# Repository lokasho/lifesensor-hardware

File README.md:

# lifesensor-hardware
Temporary repository for the next hardware generation of the CADUS Life Sensor.
Official repository at https://github.com/cadus/Life-Sensor.

## Similar projects and Resources:
- https://github.com/GliaX
- https://github.com/kitspace/awesome-electronics
- https://github.com/kitspace/kicad_footprints
- https://github.com/intajay/open-electronics

- ecg
    + https://github.com/xdever/MobilECG-II -> based on ADS1298
    + https://www.olimex.com/Products/Duino/Shields/SHIELD-EKG-EMG/open-source-hardware
    + https://www.electronicdesign.com/power-management/article/21798161/choose-the-right-resistors-for-medical-applications

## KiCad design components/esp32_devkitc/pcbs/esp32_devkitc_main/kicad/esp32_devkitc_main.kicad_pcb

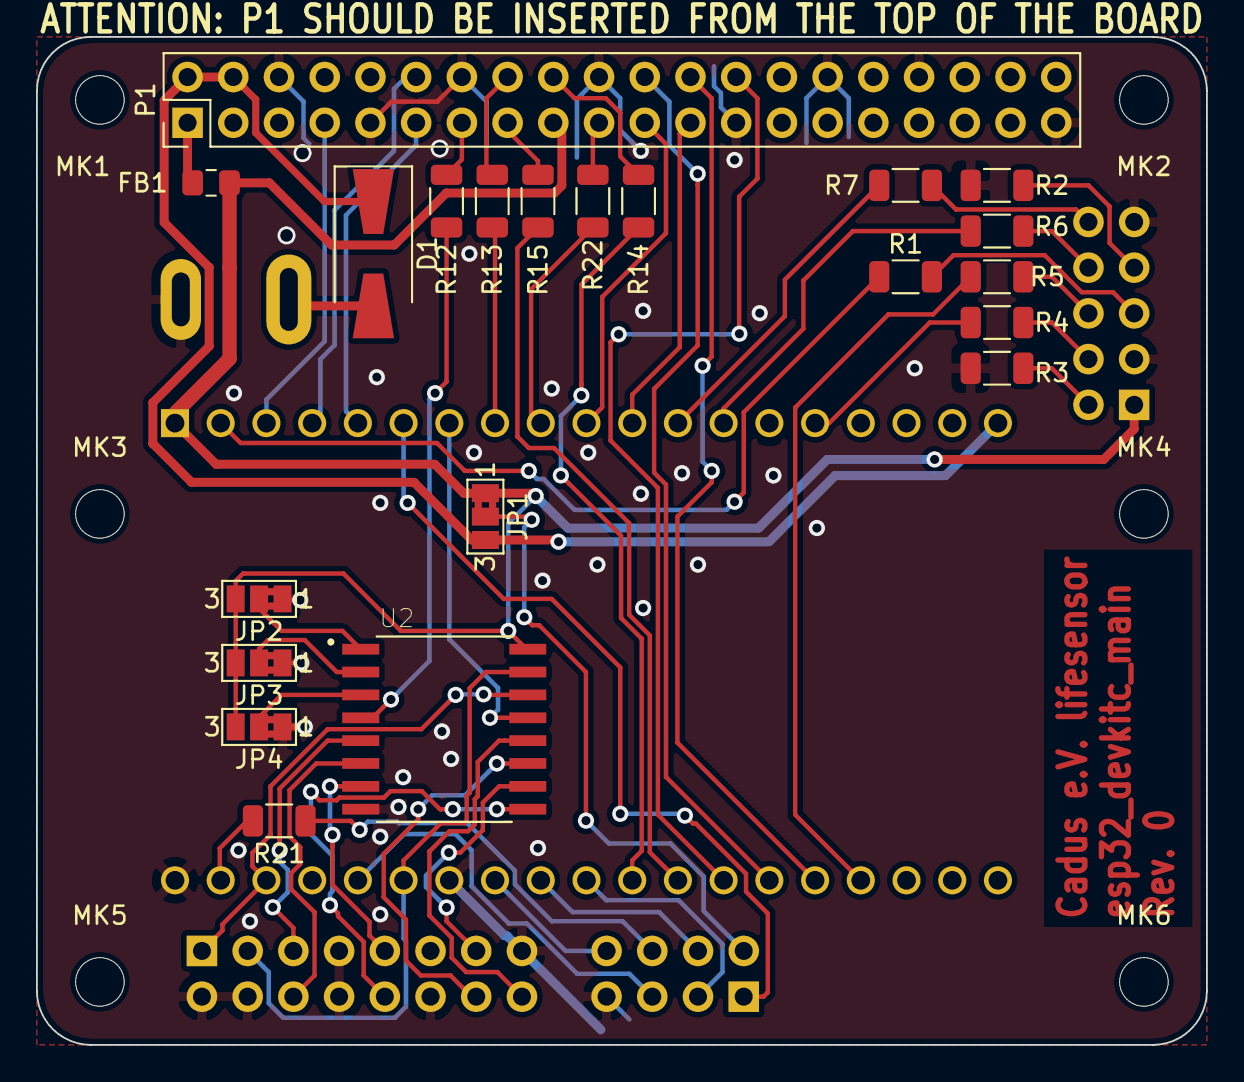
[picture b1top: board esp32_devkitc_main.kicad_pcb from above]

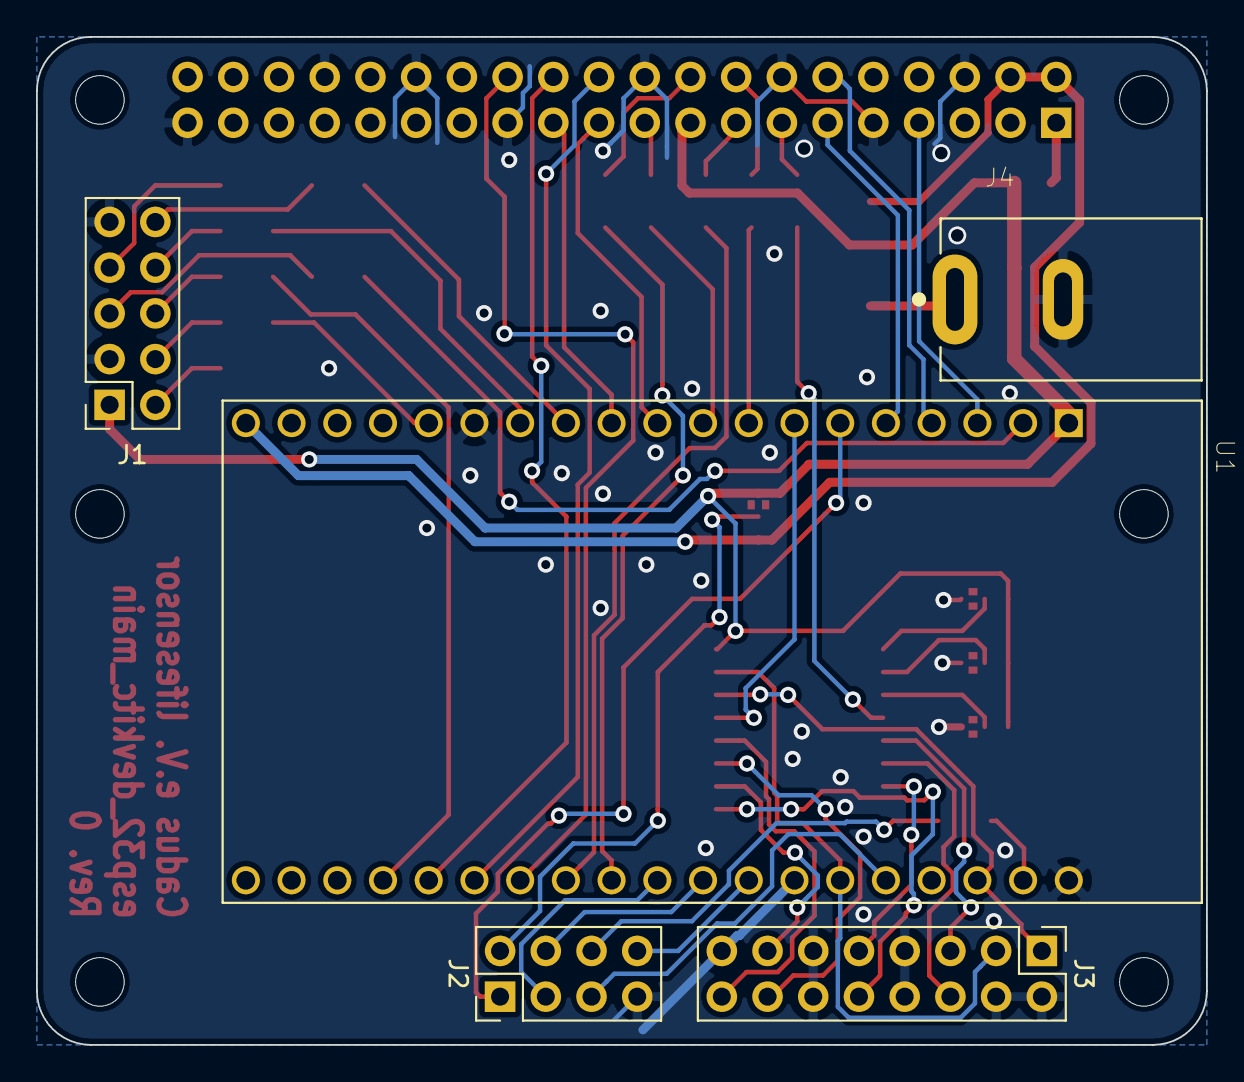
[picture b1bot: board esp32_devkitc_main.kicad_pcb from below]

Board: 2 copper layers, 65.0 x 56.0 mm, 32 parts (5 on the bottom side), 56 nets.

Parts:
D1: D; D_SMA-SMB_Universal_Handsoldering
FB1: Ferrite_Bead_Small; R_0805_2012Metric_Pad1.15x1.40mm_HandSolder
J1: Conn_02x05_Odd_Even; PinSocket_2x05_P2.54mm_Vertical
J2: Conn_02x04_Odd_Even; PinHeader_2x04_P2.54mm_Vertical
J3: Button/LED/I2C Connector; PinHeader_2x08_P2.54mm_Vertical
J4: CUI_PJ-102AH_Horizontal; CUI_PJ-037B
JP1, JP2, JP3, JP4: Jumper_NC_Dual; SolderJumper-3_P1.3mm_Bridged2Bar12_Pad1.0x1.5mm_NumberLabe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
MK1, MK2, MK3, MK4, MK5, MK6: M2.5; MountingHole_2.7mm_M2.5
P1: Conn_02x20_Odd_Even; PinHeader_2x20_P2.54mm_Vertical
R1, R3, R12, R13, R14, R15: 0; R_1206_3216Metric
R2: n.p.; R_1206_3216Metric
R4, R5, R6, R7, R21, R22: 100; R_1206_3216Metric
U1: ESP32-DEVKITC-32D; MODULE_ESP32-DEVKITC-32D
U2: PCF8574ADWR; SOIC127P1030X265-16N

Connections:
/5V_in: D1.2, J4.1
/DISP_CS_DISP: J2.3, U1.29
/DISP_CS_TOUCH: J2.5, U1.24
/DISP_INT_TOUCH: J2.1, U1.6
/DISP_MISO: J2.8, U1.27
/DISP_MOSI: J2.6, R21.1
/DISP_SCLK: J2.4, U1.28
/EXPGPIO1: J3.5, U2.5
/EXPGPIO2: J3.6, U2.6
/EXPGPIO3: J3.9, U2.7
/EXPGPIO4: J3.10, U2.9
/EXPGPIO5: J3.13, U2.10
/EXPGPIO6: J3.14, U2.11
/EXPGPIO7: J3.16, U2.12
/GPIOEXP_INT: U1.7, U2.13
/JTAG_RTCK: J1.2, R3.2
/JTAG_TCK: R4.1, U1.15
/JTAG_TDI: R6.1, U1.13
/JTAG_TDO: R5.1, U1.35
/JTAG_TMS: R7.1, U1.12
/JTAG_~SRST: J1.7, R2.1
/JTAG_~TRST: R1.1, U1.2
/PROC_SCL: J3.1, U1.22, U2.14
/PROC_SDA: J3.3, U1.25, U2.15
/SENS_3V3_ANA: FB1.2, P1.1
/SENS_3V3_DIG: FB1.1, J1.1, JP1.1, JP2.3, JP3.3, JP4.3, P1.17, U1.1, U2.16
/SENS_5V_ANA: D1.1, JP1.3, P1.2, P1.4, U1.19
/SENS_INT_BPM: P1.7, U1.3
/SENS_INT_ECG: P1.11, U1.5
/SENS_INT_SPO2: P1.12, U1.4
/SENS_MISO: P1.21, U1.10
/SENS_MOSI: P1.19, R22.1
/SENS_SCLK: P1.23, U1.11
/SENS_START: P1.13, R12.2
/~SENS_CS_BPM: P1.22, U1.33
/~SENS_CS_ECG: P1.24, U1.34
/~SENS_CS_SPO2: P1.26, U1.32
/~SENS_RST_BPM: P1.15, R15.2
/~SENS_RST_ECG: P1.16, R13.2
/~SENS_RST_SPO2: P1.18, R14.2
GND: J1.3, J1.9, J2.7, J3.2, J3.4, J3.7, J3.8, J3.11, J3.12, J3.15, J4.2, JP2.1, JP3.1, JP4.1, P1.6, P1.9, P1.14, P1.20, P1.25, P1.30, P1.34, P1.39, R2.2, R3.1, U1.14, U1.20, U1.26, U2.8
unnamed: J1.4, R4.2
unnamed: J1.5, R1.2
unnamed: J1.6, R5.2
unnamed: J1.8, R6.2
unnamed: J1.10, R7.2
unnamed: J2.2, JP1.2
unnamed: JP2.2, U2.1
unnamed: JP3.2, U2.2
unnamed: JP4.2, U2.3
unnamed: R12.1, U2.4
unnamed: R13.1, U1.8
unnamed: R14.1, U1.30
unnamed: R15.1, U1.31
unnamed: R21.2, U1.21
unnamed: R22.2, U1.9

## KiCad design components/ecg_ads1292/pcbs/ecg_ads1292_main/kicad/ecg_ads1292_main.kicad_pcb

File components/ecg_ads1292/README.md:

# lifesensor ecg_ads1292
The lifesensor ecg_ads1292 component provides a [ECG](https://en.wikipedia.org/wiki/Electrocardiography) frontent based on Texas Instruments [ADS1292](http://www.ti.com/lit/ds/symlink/ads1292.pdf).

WARNING: THIS COMPONENT DOES NOT PROVIDE ANY PROTECTION AGAINST ELECTRICAL SHOCKS! ALWAYS USE APPROPRIATE MEDICAL APPROVED POWER SUPPLIES! USE AT YOUR OWN RISK!

## Objectives
This component is developed to quickly provide a first ECG sensor that can deliver reference data for comparison with other self-developed and possibly cheaper ECG frontends. It will also provide the possibility to test other (software) components like the pulse detection and the lifesensors [sensor bus](../system/lifesensor_system.svg) with real data.
<!-- TODO: link to sensor bus description -->

To minimize the development effort integrated circuits that include all needed analog circuitry are chosen. The ADS1292 is chosen because in a search it was the cheapest one that can provide a three channel ECG found.

Due to the prototype characteristics the development of the ecg_ads1292 compontent is not focusing on low prizes, availability or repairability.

## Subcomponents

This component consists of one PCB [ecg_ads1292_main](pcbs/ecg_ads1292_main) and a [driver](firmware).

For a description of the development of the PCB see [pcbs/ecg_ads1292_main/docs/README.md](pcbs/ecg_ads1292_main/docs/README.md)

For a description of the driver see [firmware/README.md](firmware/README.md)

#### Board view
This is a view of the last released version of the board:

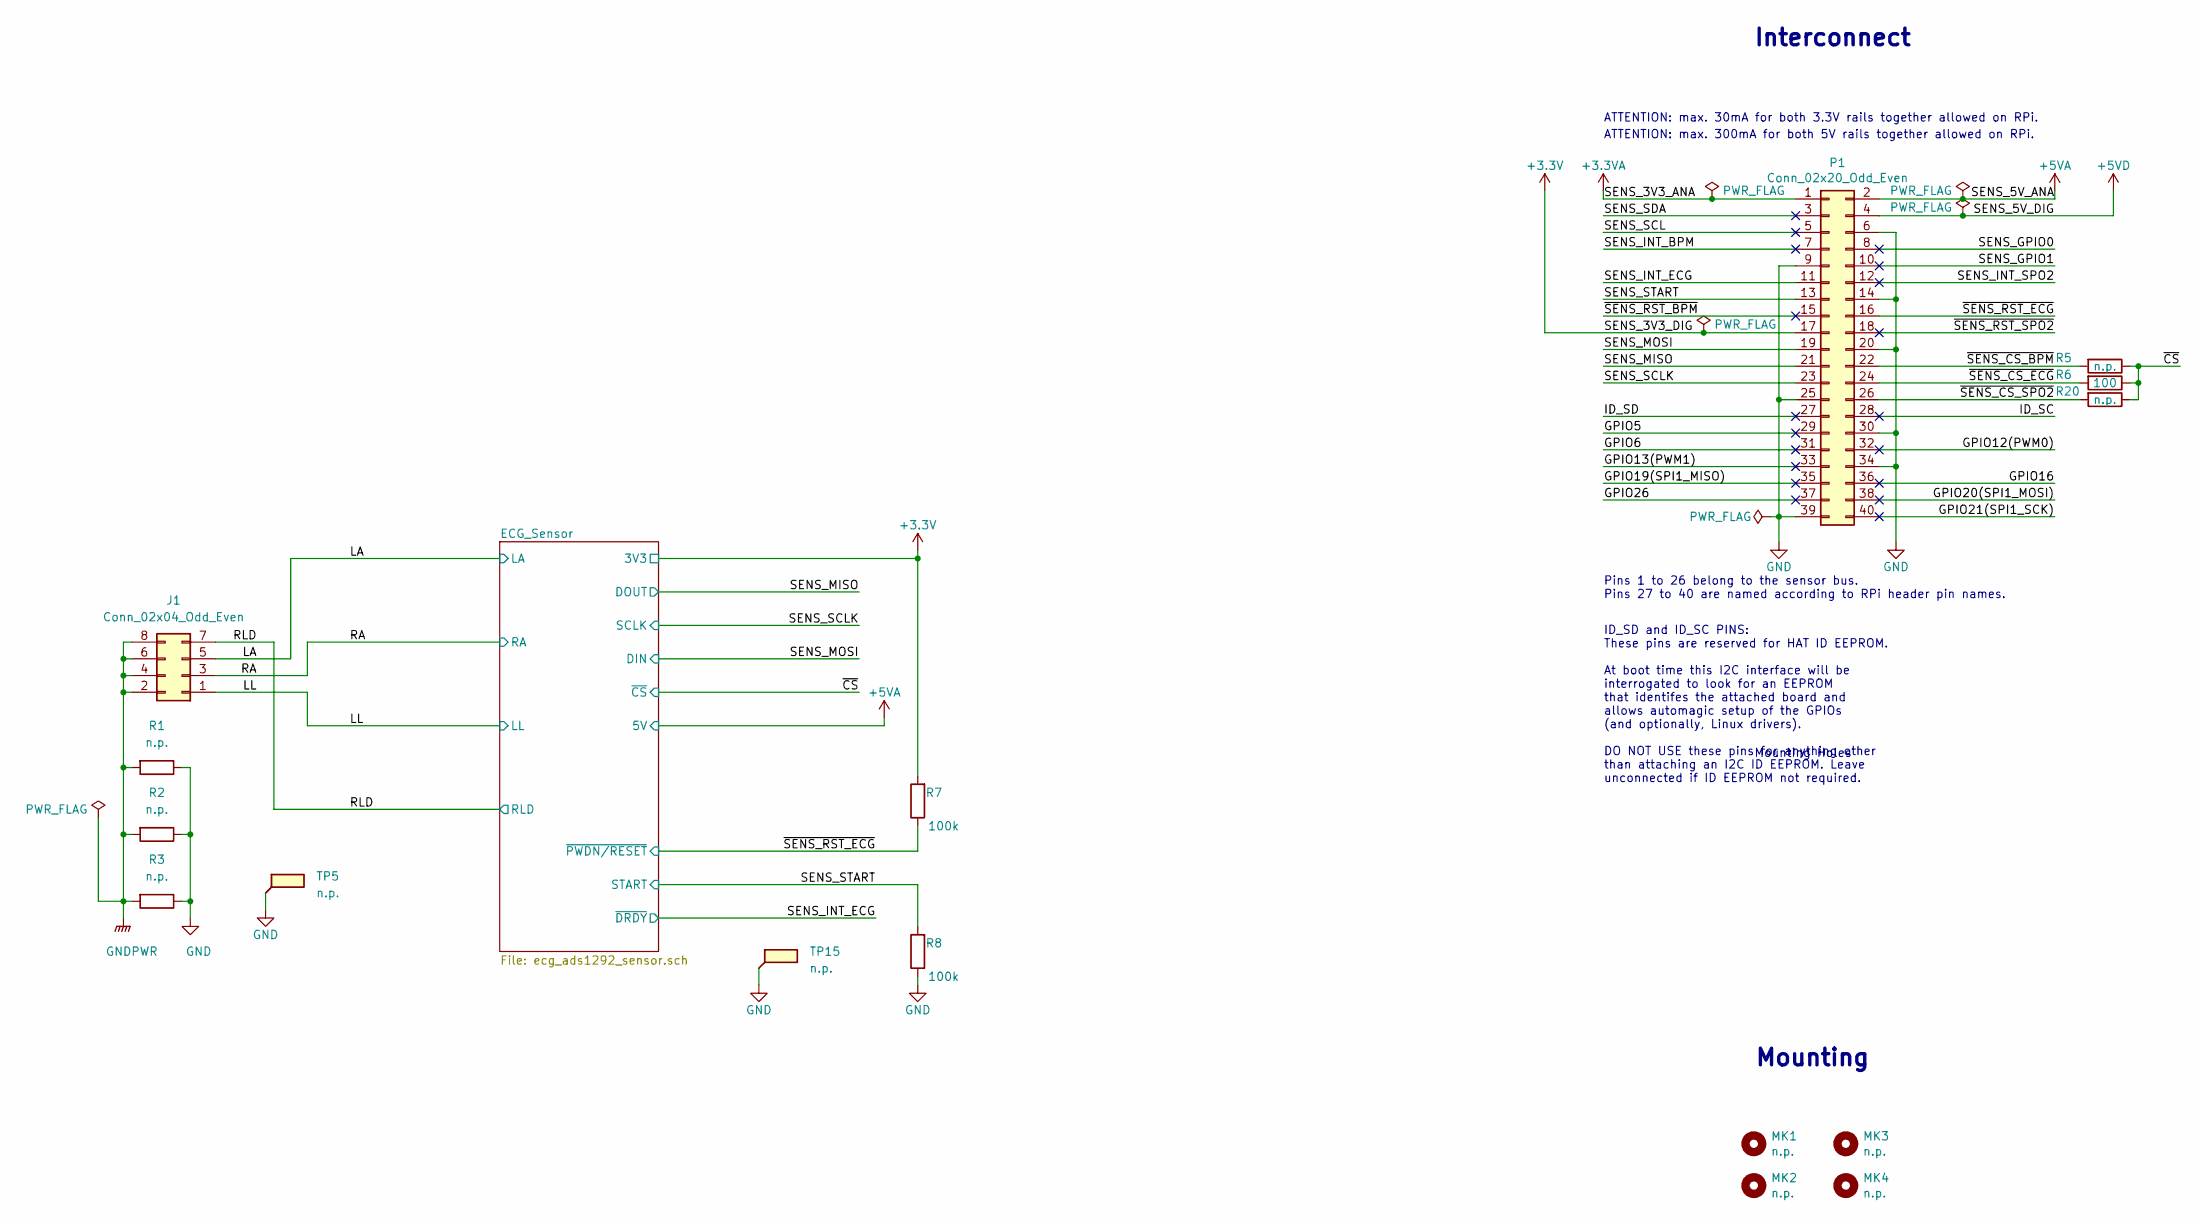
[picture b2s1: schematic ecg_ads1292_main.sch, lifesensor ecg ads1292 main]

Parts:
J1: Conn_02x04_Odd_Even; IDC-Header_2x04_P2.54mm_Horizontal; MPN TSW-104-08-T-D-RA
MK1, MK2, MK3, MK4: n.p.; MountingHole_2.7mm_M2.5
P1: Conn_02x20_Odd_Even; PinSocket_2x20_P2.54mm_Vertical; MPN 4P01-2D02-DA
R1, R2, R3: n.p.; R_0815_2038Metric_Pad1.53x4.00mm_HandSolder
R5: n.p.; R_0603_1608Metric_Pad1.05x0.95mm_HandSolder; MPN CRCW0603100RJNEA
R6: 100; R_0603_1608Metric_Pad1.05x0.95mm_HandSolder; MPN CRCW0603100RJNEA
R7, R8: 100k; R_0603_1608Metric_Pad1.05x0.95mm_HandSolder; MPN CRCW0603100KJNEA
R20: n.p.; R_0603_1608Metric_Pad1.05x0.95mm_HandSolder
TP5, TP15: n.p.; TestPoint_Loop_D2.50mm_Drill1.0mm

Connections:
+3.3VA: P1.1
+3V3: P1.17, R7.2; also elsewhere on the board
+5VA: P1.2; also elsewhere on the board
+5VD: P1.4
/GPIO5: P1.29
/GPIO6: P1.31
/GPIO12(PWM0): P1.32
/GPIO13(PWM1): P1.33
/GPIO16: P1.36
/GPIO19(SPI1_MISO): P1.35
/GPIO20(SPI1_MOSI): P1.38
/GPIO21(SPI1_SCK): P1.40
/GPIO26: P1.37
/ID_SC: P1.28
/ID_SD: P1.27
/LA: J1.5; also elsewhere on the board
/LL: J1.1; also elsewhere on the board
/RA: J1.3; also elsewhere on the board
/RLD: J1.7; also elsewhere on the board
/SENS_GPIO0: P1.8
/SENS_GPIO1: P1.10
/SENS_INT_BPM: P1.7
/SENS_INT_ECG: P1.11; also elsewhere on the board
/SENS_INT_SPO2: P1.12
/SENS_MISO: P1.21; also elsewhere on the board
/SENS_MOSI: P1.19; also elsewhere on the board
/SENS_SCL: P1.5
/SENS_SCLK: P1.23; also elsewhere on the board
/SENS_SDA: P1.3
/SENS_START: P1.13, R8.2; also elsewhere on the board
/~CS: R5.1, R6.1, R20.1; also elsewhere on the board
/~SENS_CS_BPM: P1.22, R5.2
/~SENS_CS_ECG: P1.24, R6.2
/~SENS_CS_SPO2: P1.26, R20.2
/~SENS_RST_BPM: P1.15
/~SENS_RST_ECG: P1.16, R7.1; also elsewhere on the board
/~SENS_RST_SPO2: P1.18
GND: P1.6, P1.9, P1.14, P1.20, P1.25, P1.30, P1.34, P1.39, R1.1, R2.1, R3.1, R8.1, TP5.1, TP15.1; also elsewhere on the board
GNDPWR: J1.2, J1.4, J1.6, J1.8, R1.2, R2.2, R3.2

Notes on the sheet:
ID_SD and ID_SC PINS: These pins are reserved for HAT ID EEPROM. At boot time this I2C interface will be interrogated to look for an EEPROM that identifes the attached board and allows automagic setup of the GPIOs (and optionally, Linux drivers). DO NOT USE these pins for anything other than attach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
Mounting Holes
ATTENTION: max. 30mA for both 3.3V rails together allowed on RPi.
ATTENTION: max. 300mA for both 5V rails together allowed on RPi.
Pins 1 to 26 belong to the sensor bus. Pins 27 to 40 are named according to RPi header pin names.
Interconnect
Mounting

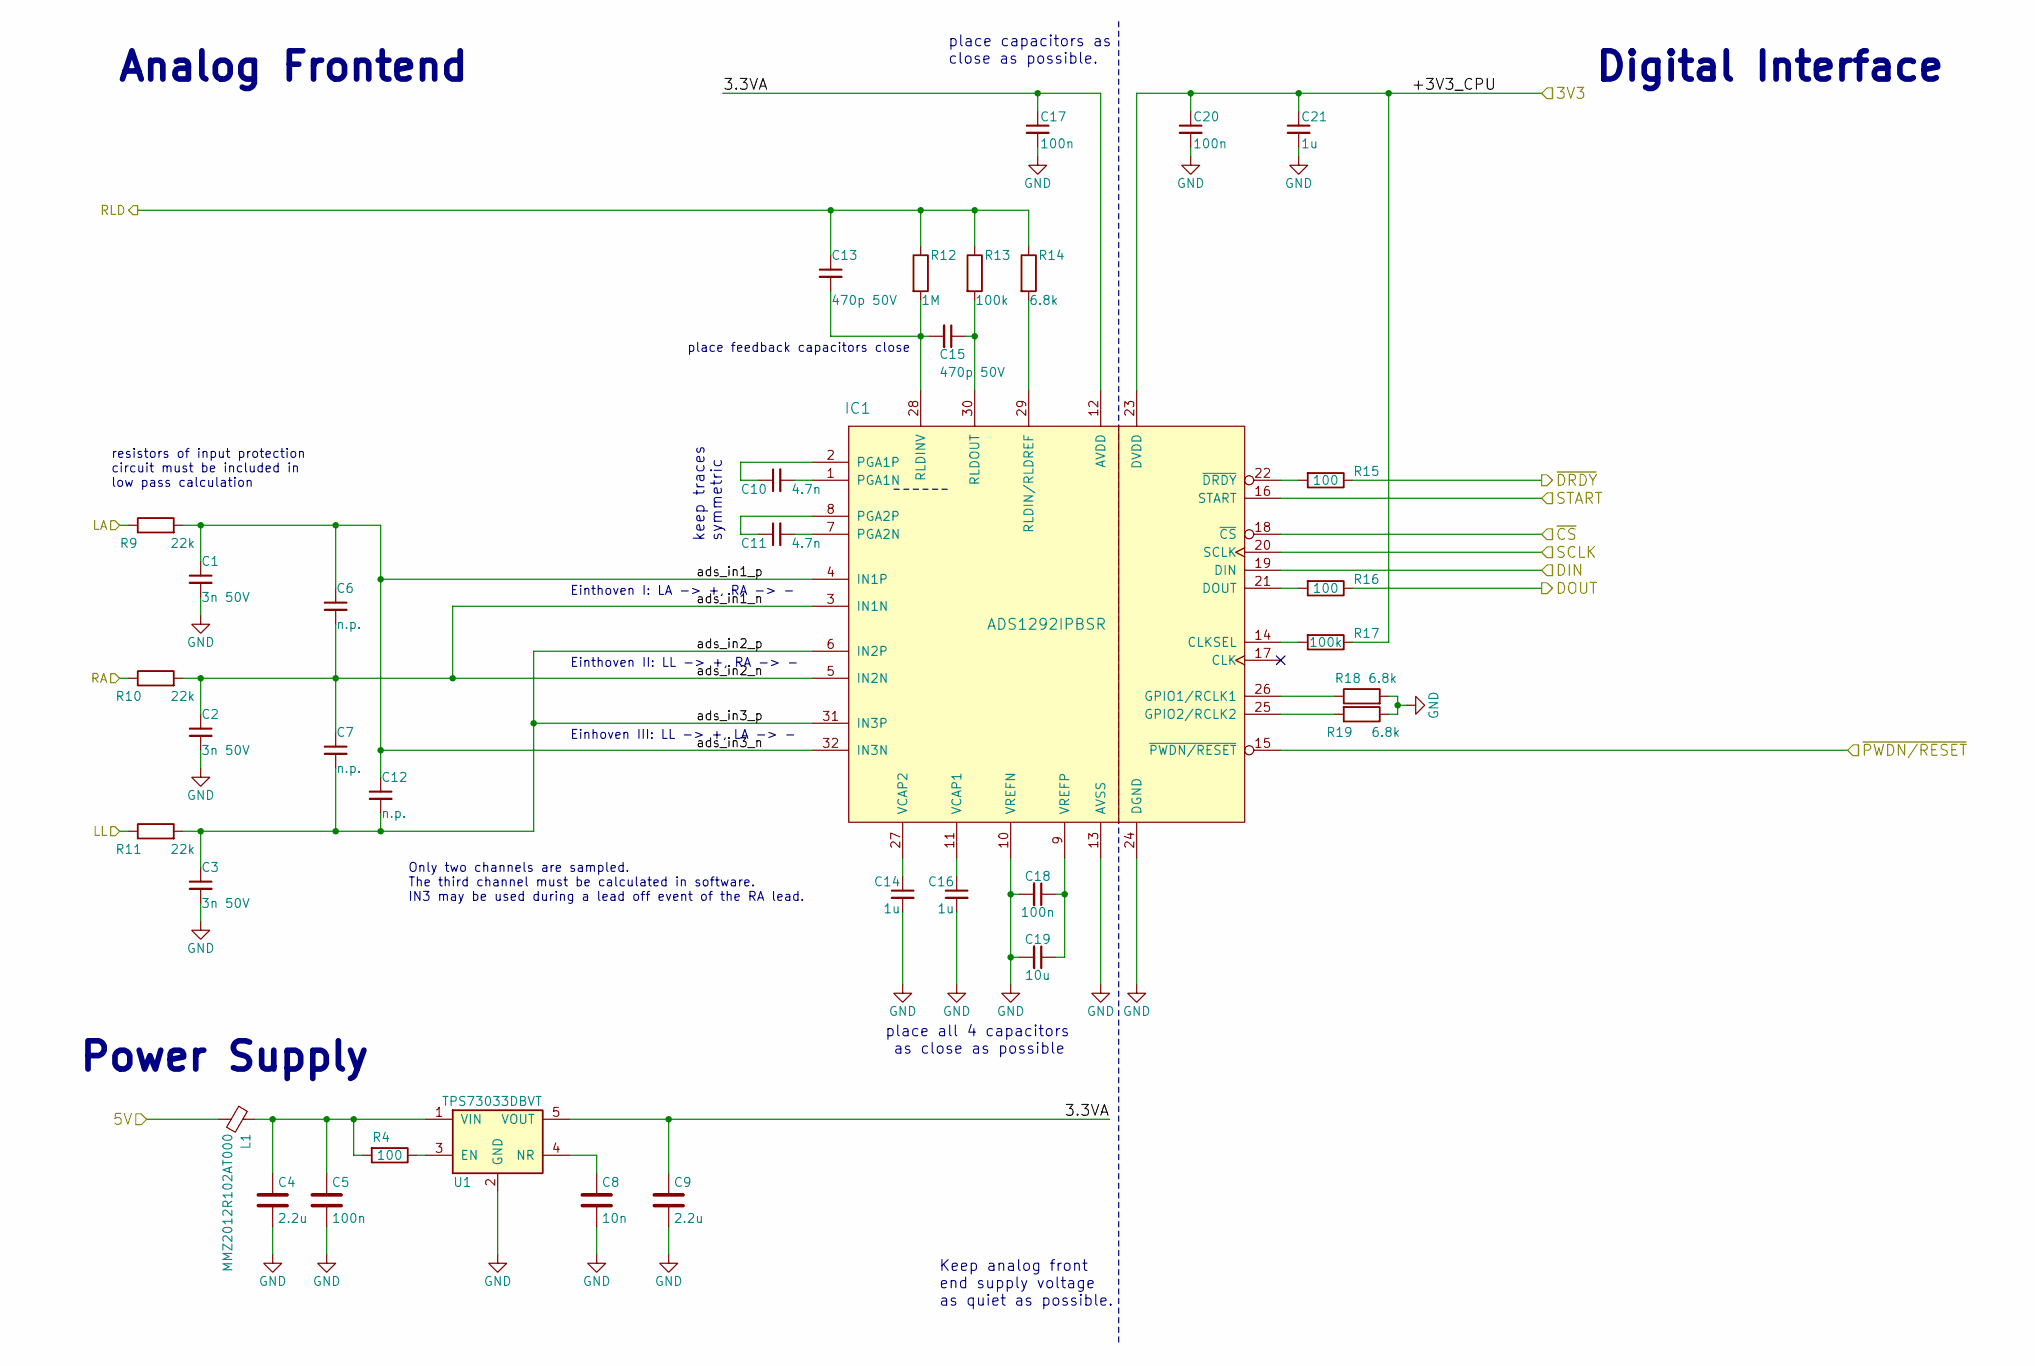
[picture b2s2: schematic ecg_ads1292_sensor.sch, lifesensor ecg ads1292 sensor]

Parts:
C1, C2, C3: 3n 50V; C_0603_1608Metric_Pad1.05x0.95mm_HandSolder; MPN C0603C302J5GAC7867
C4, C9: 2.2u; C_0603_1608Metric_Pad1.05x0.95mm_HandSolder; MPN GRM188R71A225KE15D
C5, C17, C18, C20: 100n; C_0603_1608Metric_Pad1.05x0.95mm_HandSolder; MPN C1608X7R1H104K080AA
C6, C7, C12: n.p.; C_0603_1608Metric_Pad1.05x0.95mm_HandSolder
C8: 10n; C_0603_1608Metric_Pad1.05x0.95mm_HandSolder; MPN 0603B103K101CT
C10, C11: 4.7n; C_0603_1608Metric_Pad1.05x0.95mm_HandSolder; MPN GRM1885C1H472JA01D
C13, C15: 470p 50V; C_0603_1608Metric_Pad1.05x0.95mm_HandSolder; MPN C0603C471J5GACTU
C14, C16, C21: 1u; C_0603_1608Metric_Pad1.05x0.95mm_HandSolder; MPN LMK107B7105KA-T
C19: 10u; C_0603_1608Metric_Pad1.05x0.95mm_HandSolder; MPN JMK107ABJ106KAHT
IC1: ADS1292IPBSR; LQFP-32_5x5mm_P0.5mm; MPN ADS1292IPBSR
L1: MMZ2012R102AT000; L_0805_2012Metric_Pad1.15x1.40mm_HandSolder; MPN MMZ2012R102AT000
R4, R15, R16: 100; R_0603_1608Metric_Pad1.05x0.95mm_HandSolder; MPN CRCW0603100RJNEA
R9, R10, R11: 22k; R_0603_1608Metric_Pad1.05x0.95mm_HandSolder; MPN CRCW060322K0FKEA
R12: 1M; R_0603_1608Metric_Pad1.05x0.95mm_HandSolder; MPN CRCW06031M00FKEA
R13, R17: 100k; R_0603_1608Metric_Pad1.05x0.95mm_HandSolder; MPN CRCW0603100KJNEA
R14, R18, R19: 6.8k; R_0603_1608Metric_Pad1.05x0.95mm_HandSolder; MPN CRCW06036K80FKEA
U1: TPS73033DBVT; SOT-23-5_HandSoldering

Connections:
+3V3: C20.1, C21.1, IC1.23 (DVDD), R17.1; also elsewhere on the board
+5VA: L1.2; also elsewhere on the board
/ECG_Sensor/3.3VA: C9.1, C17.1, IC1.12 (AVDD), U1.5 (VOUT)
/ECG_Sensor/ads_in1_n: C2.1, C6.2, C7.1, IC1.3 (IN1N), IC1.5 (IN2N), R10.2
/ECG_Sensor/ads_in1_p: C1.1, C6.1, C12.1, IC1.4 (IN1P), IC1.32 (IN3N), R9.2
/ECG_Sensor/ads_in2_p: C3.1, C7.2, C12.2, IC1.6 (IN2P), IC1.31 (IN3P), R11.2
/LA: R9.1; also elsewhere on the board
/LL: R11.1; also elsewhere on the board
/RA: R10.1; also elsewhere on the board
/RLD: C13.1, R12.1, R13.1, R14.1; also elsewhere on the board
/SENS_INT_ECG: R15.1; also elsewhere on the board
/SENS_MISO: R16.1; also elsewhere on the board
/SENS_MOSI: IC1.19 (DIN); also elsewhere on the board
/SENS_SCLK: IC1.20 (SCLK); also elsewhere on the board
/SENS_START: IC1.16 (START); also elsewhere on the board
/~CS: IC1.18 (~CS); also elsewhere on the board
/~SENS_RST_ECG: IC1.15 (~PWDN/RESET); also elsewhere on the board
GND: C1.2, C2.2, C3.2, C4.2, C5.2, C8.2, C9.2, C14.2, C16.2, C17.2, C18.2, C19.2, C20.2, C21.2, IC1.10 (VREFN), IC1.13 (AVSS), IC1.24 (DGND), R18.2, R19.1, U1.2 (GND); also elsewhere on the board
unnamed: C4.1, C5.1, L1.1, R4.2, U1.1 (VIN)
unnamed: C8.1, U1.4 (NR)
unnamed: C10.1, IC1.2 (PGA1P)
unnamed: C10.2, IC1.1 (PGA1N)
unnamed: C11.1, IC1.8 (PGA2P)
unnamed: C11.2, IC1.7 (PGA2N)
unnamed: C13.2, C15.2, IC1.28 (RLDINV), R12.2
unnamed: C14.1, IC1.27 (VCAP2)
unnamed: C15.1, IC1.30 (RLDOUT), R13.2
unnamed: C16.1, IC1.11 (VCAP1)
unnamed: C18.1, C19.1, IC1.9 (VREFP)
unnamed: IC1.14 (CLKSEL), R17.2
unnamed: IC1.21 (DOUT), R16.2
unnamed: IC1.22 (~DRDY), R15.2
unnamed: IC1.25 (GPIO2/RCLK2), R19.2
unnamed: IC1.26 (GPIO1/RCLK1), R18.1
unnamed: IC1.29 (RLDIN/RLDREF), R14.2
unnamed: R4.1, U1.3 (EN)

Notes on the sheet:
place all 4 capacitors as close as possible
Digital Interface
Analog Frontend
Keep analog front end supply voltage as quiet as possible.
place capacitors as close as possible.
keep traces symmetric
Power Supply
Einthoven I: LA -> +, RA -> -
Einthoven II: LL -> +, RA -> -
Einhoven III: LL -> +, LA -> -
resistors of input protection circuit must be included in low pass calculation
Only two channels are sampled. The third channel must be calculated in software. IN3 may be used during a lead off event of the RA lead.
place feedback capacitors close

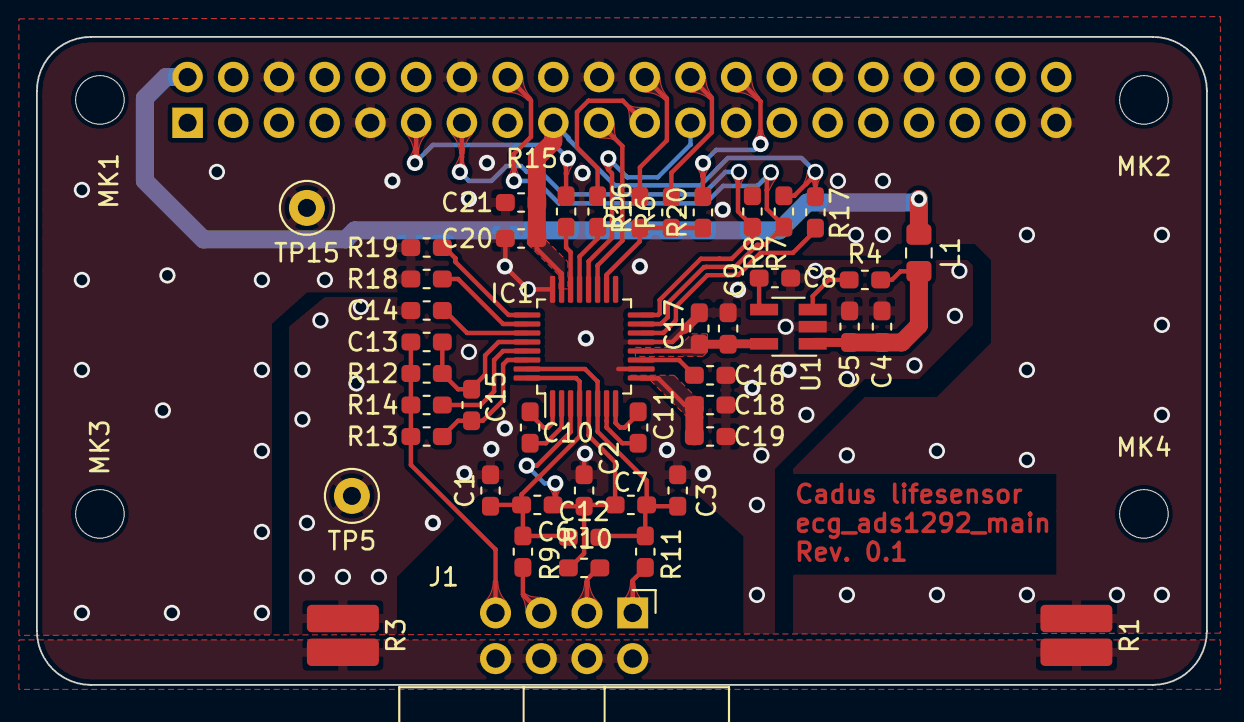
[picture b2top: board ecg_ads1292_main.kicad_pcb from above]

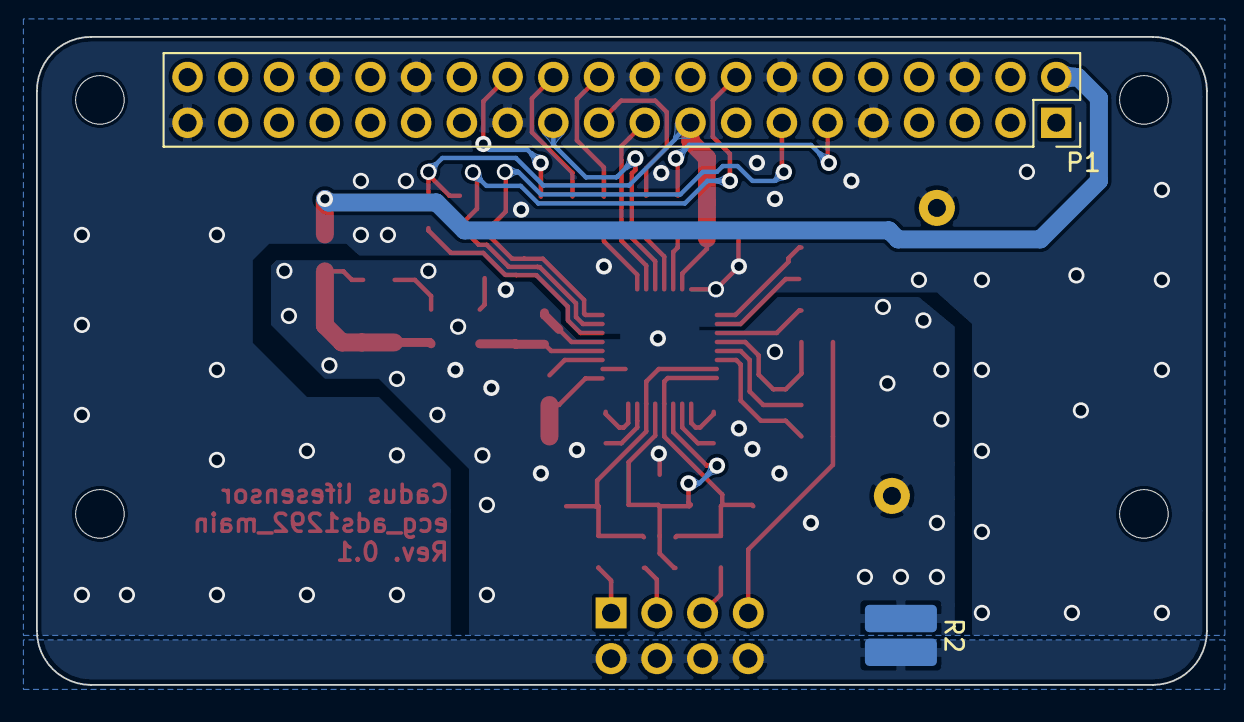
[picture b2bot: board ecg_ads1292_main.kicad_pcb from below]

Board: 2 copper layers, 65.0 x 36.0 mm, 52 parts (2 on the bottom side), 40 nets.

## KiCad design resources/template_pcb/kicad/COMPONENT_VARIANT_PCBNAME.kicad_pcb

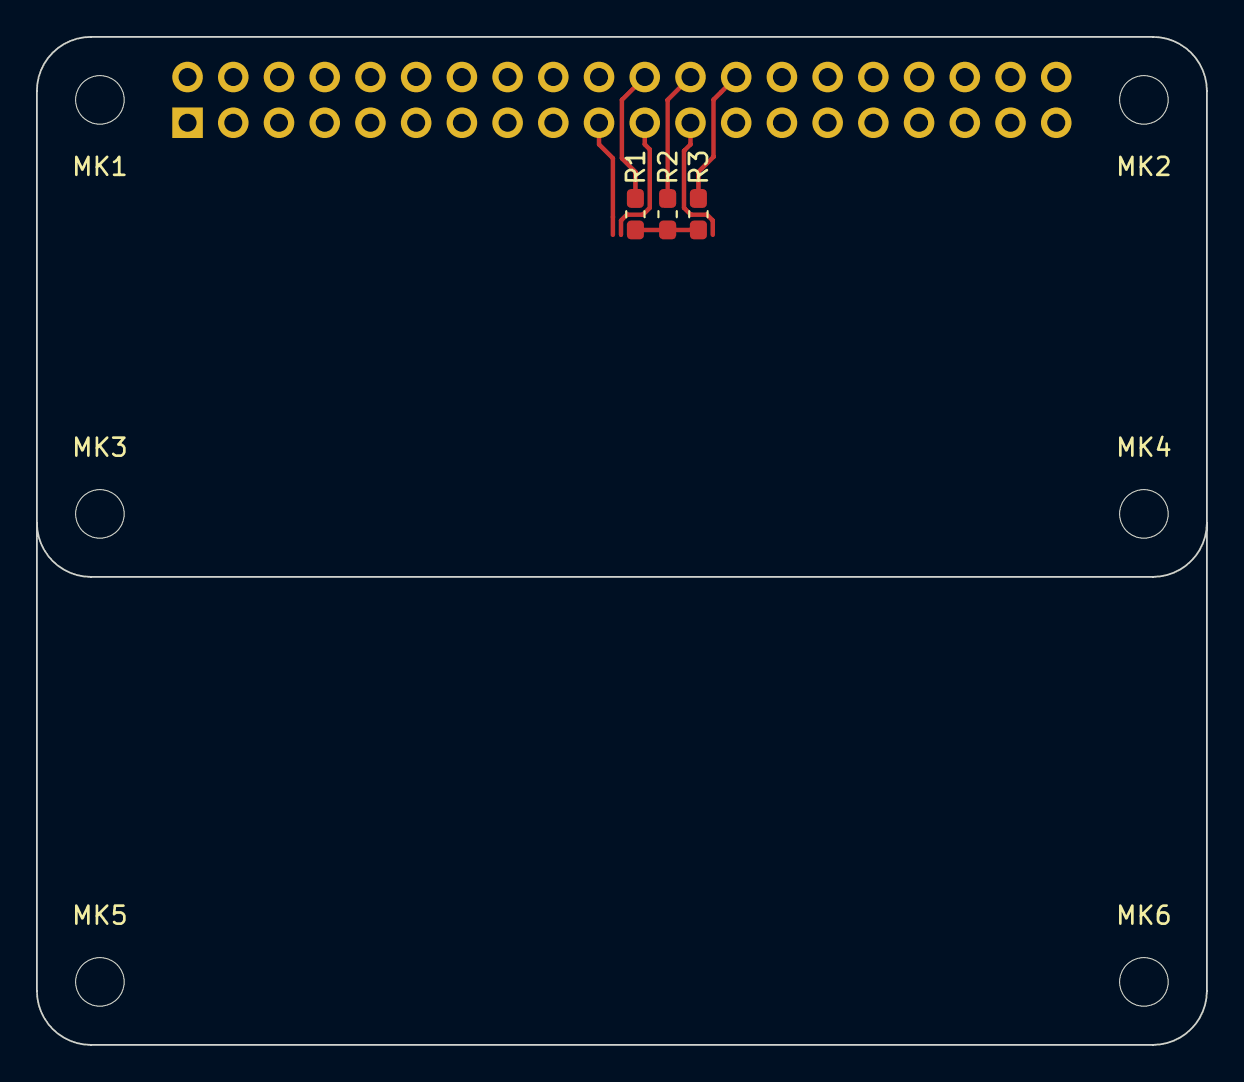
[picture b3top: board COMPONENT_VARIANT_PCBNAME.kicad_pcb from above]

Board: 2 copper layers, 65.0 x 56.0 mm, 10 parts (1 on the bottom side), 5 nets.

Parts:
MK1, MK2, MK3, MK4, MK5, MK6: M2.5; MountingHole_2.7mm_M2.5
P1: Conn_02x20_Odd_Even; PinSocket_2x20_P2.54mm_Vertical
R1, R2, R3: n.p.; R_0603_1608Metric_Pad1.05x0.95mm_HandSolder

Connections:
/~CS: R1.1, R2.1, R3.1
/~SENS_CS_BPM: P1.22, R1.2
/~SENS_CS_ECG: P1.24, R2.2
/~SENS_CS_SPO2: P1.26, R3.2
GND: P1.6, P1.9, P1.14, P1.20, P1.25, P1.30, P1.34, P1.39

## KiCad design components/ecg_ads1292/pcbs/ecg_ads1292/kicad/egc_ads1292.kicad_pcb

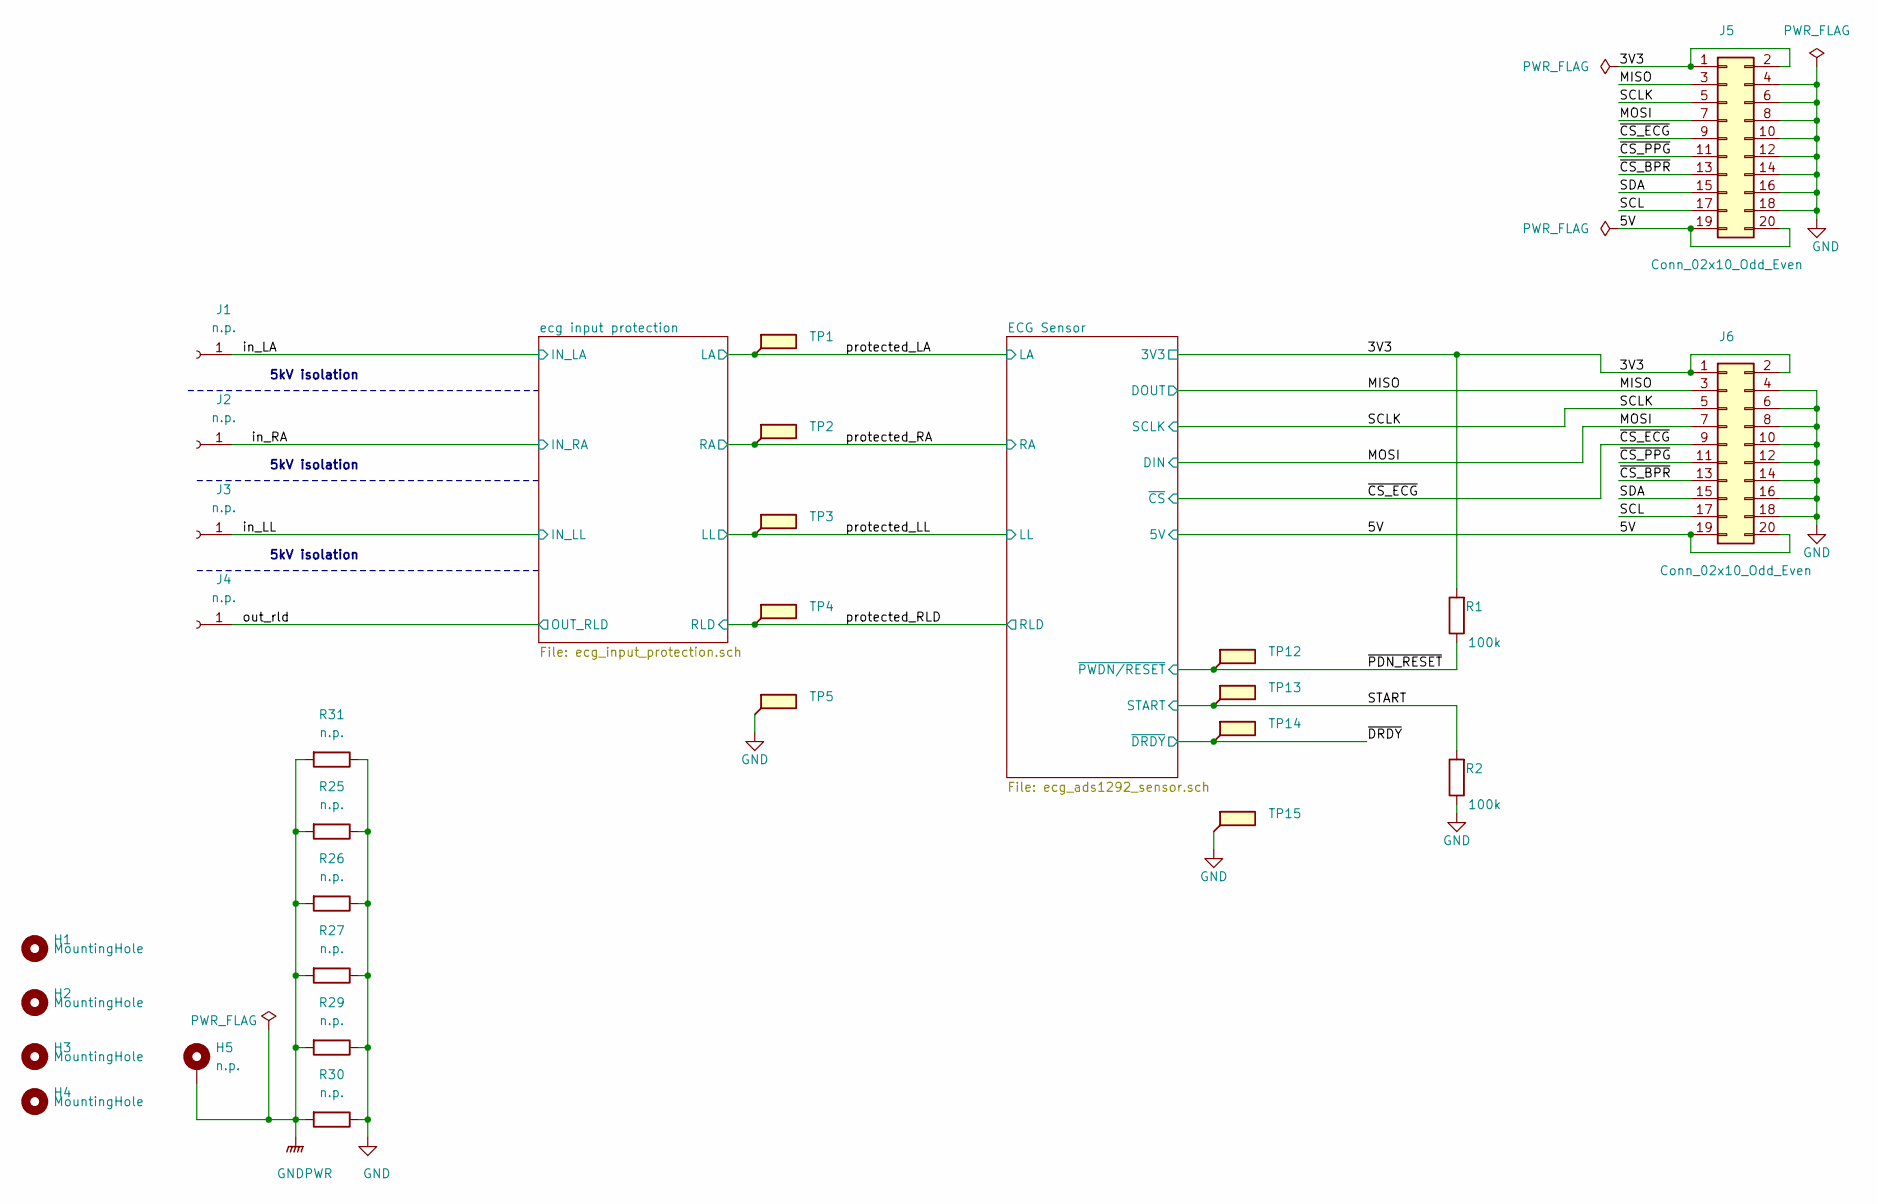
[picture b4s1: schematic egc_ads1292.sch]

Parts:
H1, H2, H3, H4: MountingHole; MountingHole_3.2mm_M3_ISO14580
H5: n.p.; MountingHole_3.2mm_M3_Pad
J1, J2, J3, J4: n.p.; PinHeader_1x01_P2.54mm_Vertical
J5, J6: Conn_02x10_Odd_Even; IDC-Header_2x10_P2.54mm_Vertical_Lock
R1, R2: 100k; R_0603_1608Metric_Pad1.05x0.95mm_HandSolder; Farnell 1738916
R25, R26, R27, R29, R30, R31: n.p.; R_0815_2038Metric_Pad1.53x4.00mm_HandSolder
TP1, TP2, TP3, TP4, TP5, TP12, TP13, TP14, TP15: TestPoint_Loop_D2.50mm_Drill1.0mm

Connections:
/3V3: J5.1, J5.2, J6.1, J6.2, R1.2; also elsewhere on the board
/5V: J5.19, J5.20, J6.19, J6.20; also elsewhere on the board
/MISO: J5.3, J6.3; also elsewhere on the board
/MOSI: J5.7, J6.7; also elsewhere on the board
/SCL: J5.17, J6.17
/SCLK: J5.5, J6.5; also elsewhere on the board
/SDA: J5.15, J6.15
/START: R2.2, TP13.1; also elsewhere on the board
/in_LA: J1.1; also elsewhere on the board
/in_LL: J3.1; also elsewhere on the board
/in_RA: J2.1; also elsewhere on the board
/out_rld: J4.1; also elsewhere on the board
/protected_LA: TP1.1; also elsewhere on the board
/protected_LL: TP3.1; also elsewhere on the board
/protected_RA: TP2.1; also elsewhere on the board
/protected_RLD: TP4.1; also elsewhere on the board
/~CS_BPR: J5.13, J6.13
/~CS_ECG: J5.9, J6.9; also elsewhere on the board
/~CS_PPG: J5.11, J6.11
/~DRDY: TP14.1; also elsewhere on the board
/~PDN_RESET: R1.1, TP12.1; also elsewhere on the board
GND: J5.4, J5.6, J5.8, J5.10, J5.12, J5.14, J5.16, J5.18, J6.4, J6.6, J6.8, J6.10, J6.12, J6.14, J6.16, J6.18, R2.1, R25.1, R26.1, R27.1, R29.1, R30.1, R31.1, TP5.1, TP15.1; also elsewhere on the board
GNDPWR: H5.1, R25.2, R26.2, R27.2, R29.2, R30.2, R31.2; also elsewhere on the board

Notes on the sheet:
5kV isolation
